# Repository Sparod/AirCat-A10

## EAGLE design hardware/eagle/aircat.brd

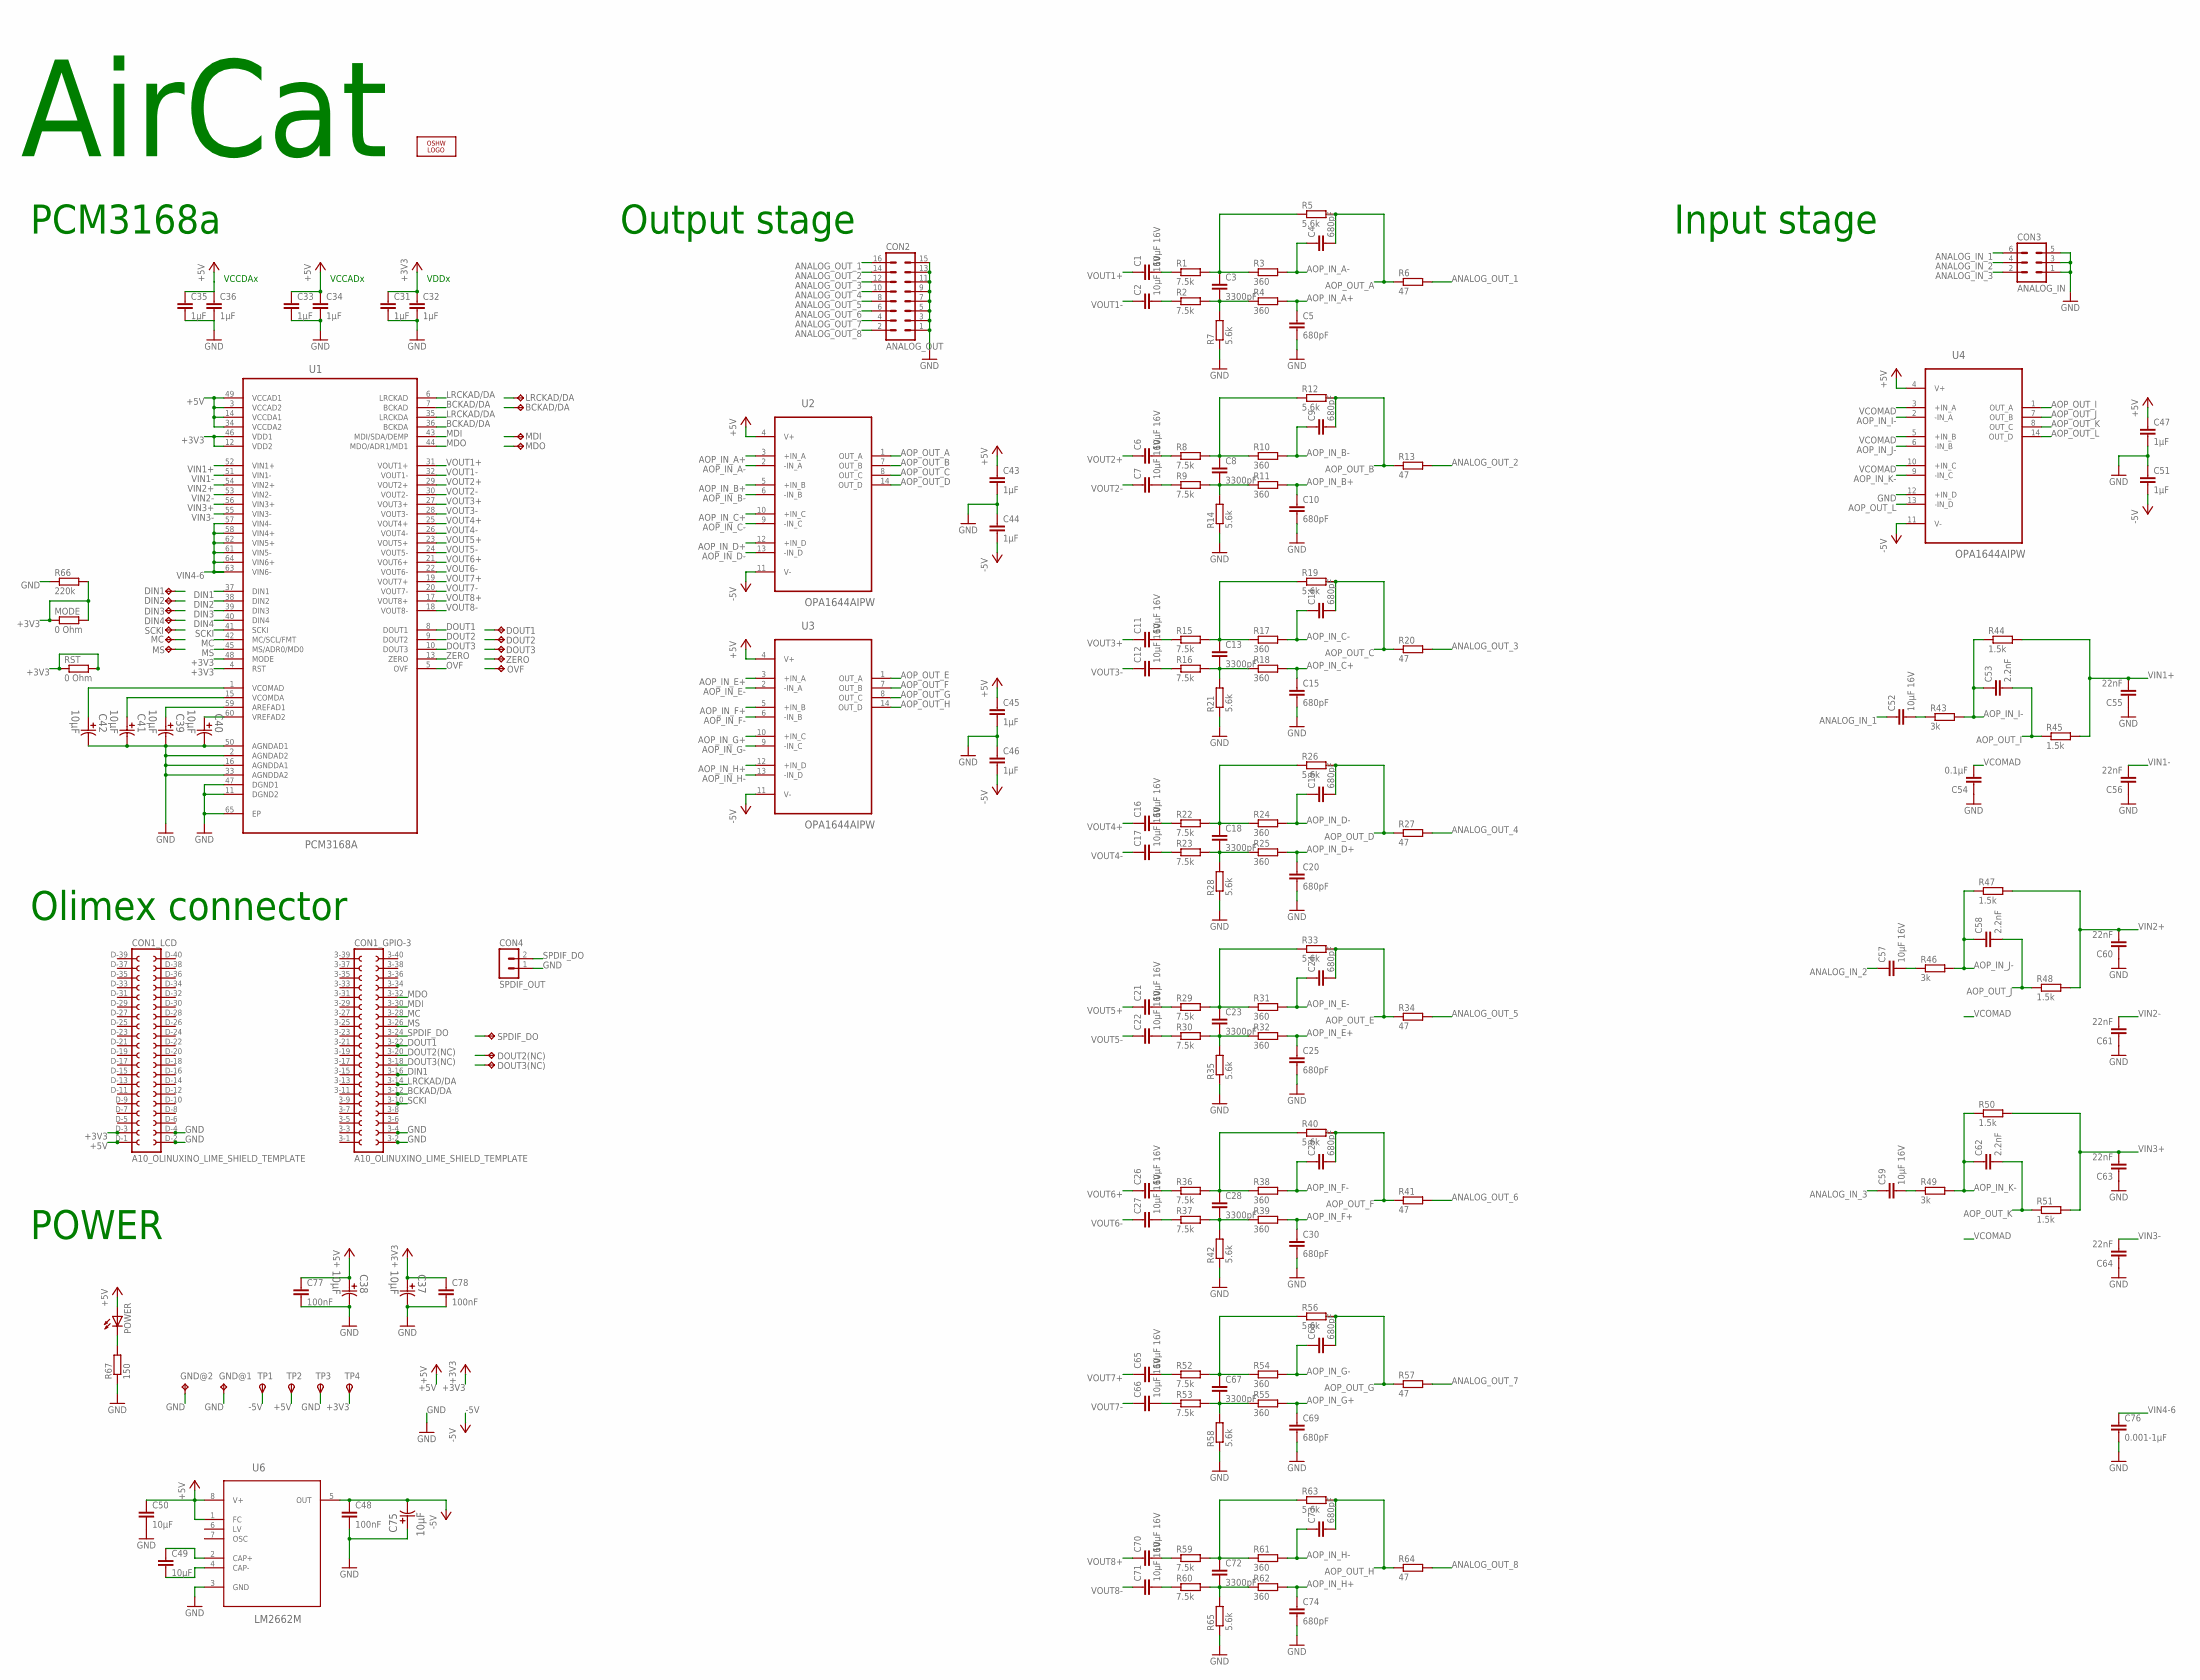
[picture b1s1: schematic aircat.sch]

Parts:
BCKAD/DA: TPTP10SQ; TP10SQ
C1, C2, C6, C7, C11, C12, C16, C17, C21, C22, C26, C27, C52, C57, C59, C65, C66, C70, C71: 10µF 16V; C0805; MPN 1206YD106KAT2A
C3, C8, C13, C18, C23, C28, C67, C72: 3300pF; C0603; MPN 06035C332KAT2A
C4, C5, C9, C10, C14, C15, C19, C20, C24, C25, C29, C30, C68, C69, C73, C74: 680pF; C0603; MPN C0603C681J5GACTU
C31, C32, C33, C34, C35, C36, C43, C44, C45, C46, C47, C51: 1µF; C0603; MPN 0603ZD105KAT2A
C37: 10µF; CAPAE430X610N; MPN EEEFK1V100UR
C38, C39, C40, C41, C42, C75: 10µF; CAPAE430X610N; TOLERANCE ±20 %; VOLTAGERATING 35V; MPN EEEFK1V100UR
C48: 100nF; C0603; MPN 10SVP10M
C49, C50: 10µF; C0805; MPN 10SVP10M
C53, C58, C62: 2.2nF; C0603; MPN 06035C222KAT2A
C54: 0.1µF; C0603; MPN 0402YD104KAT2A
C55, C56, C60, C61, C63, C64: 22nF; C0603; MPN 06033C223KAT2A
C76: 0.001-1µF; C0603
C77, C78: 100nF; C0603; MPN 06033D104KAT2A
CON1: A10_OLINUXINO_LIME_SHIELD_TEMPLATE; A10_OLINUXINO_LIME_SHIELD
CON2: ANALOG_OUT; MA08-2
CON3: ANALOG_IN; MA03-2
CON4: SPDIF_OUT; MA02-1
DIN1, DIN2, DIN3, DIN4: TPTP10SQ; TP10SQ
DOUT1, DOUT2, DOUT2(NC), DOUT3, DOUT3(NC): TPTP10SQ; TP10SQ
GND@1, GND@2: TPTP10SQ; TP10SQ
LOGO1: OSHW_LOGO_FILLX0200-NT; OSHW_FILLX200_NOTEXT
LRCKAD/DA: TPTP10SQ; TP10SQ
MC: TPTP10SQ; TP10SQ
MDI: TPTP10SQ; TP10SQ
MDO: TPTP10SQ; TP10SQ
MODE: 0 Ohm; R0603
MS: TPTP10SQ; TP10SQ
OVF: TPTP10SQ; TP10SQ
POWER: LEDSML0603; SML0603
R1, R2, R8, R9, R15, R16, R22, R23, R29, R30, R36, R37, R52, R53, R59, R60: 7.5k; R0603; MPN MCRE000161
R3, R4, R10, R11, R17, R18, R24, R25, R31, R32, R38, R39, R54, R55, R61, R62: 360; R0603
R5, R7, R12, R14, R19, R21, R26, R28, R33, R35, R40, R42, R56, R58, R63, R65: 5.6k; R0603; MPN MCPWR05FTEW5601
R6, R13, R20, R27, R34, R41, R57, R64: 47; R0603
R43, R46, R49: 3k; R0603; MPN 167I 3K TX 9 X 80 MM
R44, R45, R47, R48, R50, R51: 1.5k; R0603
R66: 220k; R0603
R67: 150; R0603; MPN MCRE000161
RST: 0 Ohm; R0603
SCKI: TPTP10SQ; TP10SQ
SPDIF_DO: TPTP10SQ; TP10SQ
TP1: -5V; B1,27
TP2: +5V; B1,27
TP3: GND; B1,27
TP4: +3V3; B1,27
U1: PCM3168A; QFP50P1200X1200X120-65N; MPN PCM3168APAP
U2, U3, U4: OPA1644AIPW; SOP65P640X120-14N; MPN OPA1644AIPW
U6: LM2662M; SOIC127P620X175-8N; MPN LM2662M
ZERO: TPTP10SQ; TP10SQ

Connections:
+3V3: C31.1, C32.1, C37.1, C78.1, CON1.D-3 (3), MODE.1, MODE.2, R66.2, RST.1, RST.2, TP4.TP, U1.4 (RST), U1.12 (VDD2), U1.46 (VDD1), U1.48 (MODE)
+5V: C33.1, C34.1, C35.1, C36.1, C38.1, C43.1, C45.1, C47.1, C50.1, C77.1, CON1.D-1 (1), POWER.A, TP2.TP, U1.3 (VCCAD2), U1.14 (VCCDA1), U1.34 (VCCDA2), U1.49 (VCCAD1), U2.4 (V+), U3.4 (V+), U4.4 (V+), U6.1 (FC), U6.8 (V+)
-5V: C44.2, C46.2, C48.1, C51.2, C75.2, TP1.TP, U2.11 (V-), U3.11 (V-), U4.11 (V-), U6.5 (OUT)
ANALOG_IN_1: C52.1, CON3.6
ANALOG_IN_2: C57.1, CON3.4
ANALOG_IN_3: C59.1, CON3.2
ANALOG_OUT_1: CON2.16, R6.2
ANALOG_OUT_2: CON2.14, R13.2
ANALOG_OUT_3: CON2.12, R20.2
ANALOG_OUT_4: CON2.10, R27.2
ANALOG_OUT_5: CON2.8, R34.2
ANALOG_OUT_6: CON2.6, R41.2
ANALOG_OUT_7: CON2.4, R57.2
ANALOG_OUT_8: CON2.2, R64.2
AOP_IN_A+: C5.1, R4.2, U2.3 (+IN_A)
AOP_IN_A-: C4.1, R3.2, U2.2 (-IN_A)
AOP_IN_B+: C10.1, R11.2, U2.5 (+IN_B)
AOP_IN_B-: C9.1, R10.2, U2.6 (-IN_B)
AOP_IN_C+: C15.1, R18.2, U2.10 (+IN_C)
AOP_IN_C-: C14.1, R17.2, U2.9 (-IN_C)
AOP_IN_D+: C20.1, R25.2, U2.12 (+IN_D)
AOP_IN_D-: C19.1, R24.2, U2.13 (-IN_D)
AOP_IN_E+: C25.1, R32.2, U3.3 (+IN_A)
AOP_IN_E-: C24.1, R31.2, U3.2 (-IN_A)
AOP_IN_F+: C30.1, R39.2, U3.5 (+IN_B)
AOP_IN_F-: C29.1, R38.2, U3.6 (-IN_B)
AOP_IN_G+: C69.1, R55.2, U3.10 (+IN_C)
AOP_IN_G-: C68.1, R54.2, U3.9 (-IN_C)
AOP_IN_H+: C74.1, R62.2, U3.12 (+IN_D)
AOP_IN_H-: C73.1, R61.2, U3.13 (-IN_D)
AOP_IN_I-: C53.1, R43.2, R44.1, U4.2 (-IN_A)
AOP_IN_J-: C58.1, R46.2, R47.1, U4.6 (-IN_B)
AOP_IN_K-: C62.1, R49.2, R50.1, U4.9 (-IN_C)
AOP_OUT_A: C4.2, R5.2, R6.1, U2.1 (OUT_A)
AOP_OUT_B: C9.2, R12.2, R13.1, U2.7 (OUT_B)
AOP_OUT_C: C14.2, R19.2, R20.1, U2.8 (OUT_C)
AOP_OUT_D: C19.2, R26.2, R27.1, U2.14 (OUT_D)
AOP_OUT_E: C24.2, R33.2, R34.1, U3.1 (OUT_A)
AOP_OUT_F: C29.2, R40.2, R41.1, U3.7 (OUT_B)
AOP_OUT_G: C68.2, R56.2, R57.1, U3.8 (OUT_C)
AOP_OUT_H: C73.2, R63.2, R64.1, U3.14 (OUT_D)
AOP_OUT_I: C53.2, R45.1, U4.1 (OUT_A)
AOP_OUT_J: C58.2, R48.1, U4.7 (OUT_B)
AOP_OUT_K: C62.2, R51.1, U4.8 (OUT_C)
AOP_OUT_L: U4.13 (-IN_D), U4.14 (OUT_D)
AREFAD1: C39.1, U1.59 (AREFAD1)
BCKAD/DA: BCKAD/DA.TP, CON1.3-12 (12), U1.7 (BCKAD), U1.36 (BCKDA)
DIN1: CON1.3-16 (16), DIN1.TP, U1.37 (DIN1)
DIN2: DIN2.TP, U1.38 (DIN2)
DIN3: DIN3.TP, U1.39 (DIN3)
DIN4: DIN4.TP, U1.40 (DIN4)
DOUT1: CON1.3-22 (22), DOUT1.TP, U1.8 (DOUT1)
DOUT2: DOUT2.TP, U1.9 (DOUT2)
DOUT2(NC): CON1.3-20 (20), DOUT2(NC).TP
DOUT3: DOUT3.TP, U1.10 (DOUT3)
DOUT3(NC): CON1.3-18 (18), DOUT3(NC).TP
GND: C5.2, C10.2, C15.2, C20.2, C25.2, C30.2, C31.2, C32.2, C33.2, C34.2, C35.2, C36.2, C37.2, C38.2, C39.2, C40.2, C41.2, C42.2, C43.2, C44.1, C45.2, C46.1, C47.2, C48.2, C50.2, C51.1, C54.1, C55.1, C56.1, C60.1, C61.1, C63.1, C64.1, C69.2, C74.2, C75.1, C76.2, C77.2, C78.2, CON1.3-2 (2), CON1.3-4 (4), CON1.D-2 (2), CON1.D-4 (4), CON2.1, CON2.3, CON2.5, CON2.7, CON2.9, CON2.11, CON2.13, CON2.15, CON3.1, CON3.3, CON3.5, CON4.1, GND@1.TP, GND@2.TP, R7.1, R14.1, R21.1, R28.1, R35.1, R42.1, R58.1, R65.1, R66.1, R67.1, TP3.TP, U1.2 (AGNDAD2), U1.11 (DGND2), U1.16 (AGNDDA1), U1.33 (AGNDDA2), U1.47 (DGND1), U1.50 (AGNDAD1), U1.65 (EP), U4.12 (+IN_D), U6.3 (GND)
LRCKAD/DA: CON1.3-14 (14), LRCKAD/DA.TP, U1.6 (LRCKAD), U1.35 (LRCKDA)
MC: CON1.3-28 (28), MC.TP, U1.42 (MC/SCL/FMT)
MDI: CON1.3-30 (30), MDI.TP, U1.43 (MDI/SDA/DEMP)
MDO: CON1.3-32 (32), MDO.TP, U1.44 (MDO/ADR1/MD1)
MS: CON1.3-26 (26), MS.TP, U1.45 (MS/ADR0/MD0)
unnamed: C2.2, R2.1
unnamed: C1.2, R1.1
unnamed: C3.1, R1.2, R3.1, R5.1
unnamed: C3.2, R2.2, R4.1, R7.2
unnamed: C7.2, R9.1
unnamed: C6.2, R8.1
unnamed: C8.1, R8.2, R10.1, R12.1
unnamed: C8.2, R9.2, R11.1, R14.2
unnamed: C12.2, R16.1
unnamed: C11.2, R15.1
unnamed: C13.1, R15.2, R17.1, R19.1
unnamed: C13.2, R16.2, R18.1, R21.2
unnamed: C17.2, R23.1
unnamed: C16.2, R22.1
unnamed: C18.1, R22.2, R24.1, R26.1
unnamed: C18.2, R23.2, R25.1, R28.2
unnamed: C22.2, R30.1
unnamed: C21.2, R29.1
unnamed: C23.1, R29.2, R31.1, R33.1
unnamed: C23.2, R30.2, R32.1, R35.2
unnamed: C27.2, R37.1
unnamed: C26.2, R36.1
unnamed: C28.1, R36.2, R38.1, R40.1
unnamed: C28.2, R37.2, R39.1, R42.2
unnamed: C52.2, R43.1
unnamed: C57.2, R46.1
unnamed: C59.2, R49.1
unnamed: C66.2, R53.1
unnamed: C65.2, R52.1
unnamed: C67.1, R52.2, R54.1, R56.1
unnamed: C67.2, R53.2, R55.1, R58.2
unnamed: C71.2, R60.1
unnamed: C70.2, R59.1
unnamed: C49.1, U6.2 (CAP+)
unnamed: C49.2, U6.4 (CAP-)
unnamed: C72.1, R59.2, R61.1, R63.1
unnamed: C72.2, R60.2, R62.1, R65.2
unnamed: POWER.C, R67.2
OVF: OVF.TP, U1.5 (OVF)
SCKI: CON1.3-10 (10), SCKI.TP, U1.41 (SCKI)
SPDIF_DO: CON1.3-24 (24), CON4.2, SPDIF_DO.TP
VCOMAD: C42.1, C54.2, U1.1 (VCOMAD), U4.3 (+IN_A), U4.5 (+IN_B), U4.10 (+IN_C)
VCOMDA: C41.1, U1.15 (VCOMDA)
VIN1+: C55.2, R44.2, R45.2, U1.52 (VIN1+)
VIN1-: C56.2, U1.51 (VIN1-)
VIN2+: C60.2, R47.2, R48.2, U1.54 (VIN2+)
VIN2-: C61.2, U1.53 (VIN2-)
VIN3+: C63.2, R50.2, R51.2, U1.56 (VIN3+)
VIN3-: C64.2, U1.55 (VIN3-)
VIN4-6: C76.1, U1.57 (VIN4-), U1.58 (VIN4+), U1.61 (VIN5-), U1.62 (VIN5+), U1.63 (VIN6-), U1.64 (VIN6+)
VOUT1+: C1.1, U1.31 (VOUT1+)
VOUT1-: C2.1, U1.32 (VOUT1-)
VOUT2+: C6.1, U1.29 (VOUT2+)
VOUT2-: C7.1, U1.30 (VOUT2-)
VOUT3+: C11.1, U1.27 (VOUT3+)
VOUT3-: C12.1, U1.28 (VOUT3-)
VOUT4+: C16.1, U1.25 (VOUT4+)
VOUT4-: C17.1, U1.26 (VOUT4-)
VOUT5+: C21.1, U1.23 (VOUT5+)
VOUT5-: C22.1, U1.24 (VOUT5-)
VOUT6+: C26.1, U1.21 (VOUT6+)
VOUT6-: C27.1, U1.22 (VOUT6-)
VOUT7+: C65.1, U1.19 (VOUT7+)
VOUT7-: C66.1, U1.20 (VOUT7-)
VOUT8+: C70.1, U1.17 (VOUT8+)
VOUT8-: C71.1, U1.18 (VOUT8-)
VREFAD2: C40.1, U1.60 (VREFAD2)
ZERO: U1.13 (ZERO), ZERO.TP

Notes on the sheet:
VCCDAx
VCCADx
VDDx
POWER
Olimex connector
PCM3168a
Output stage
Input stage
AirCat

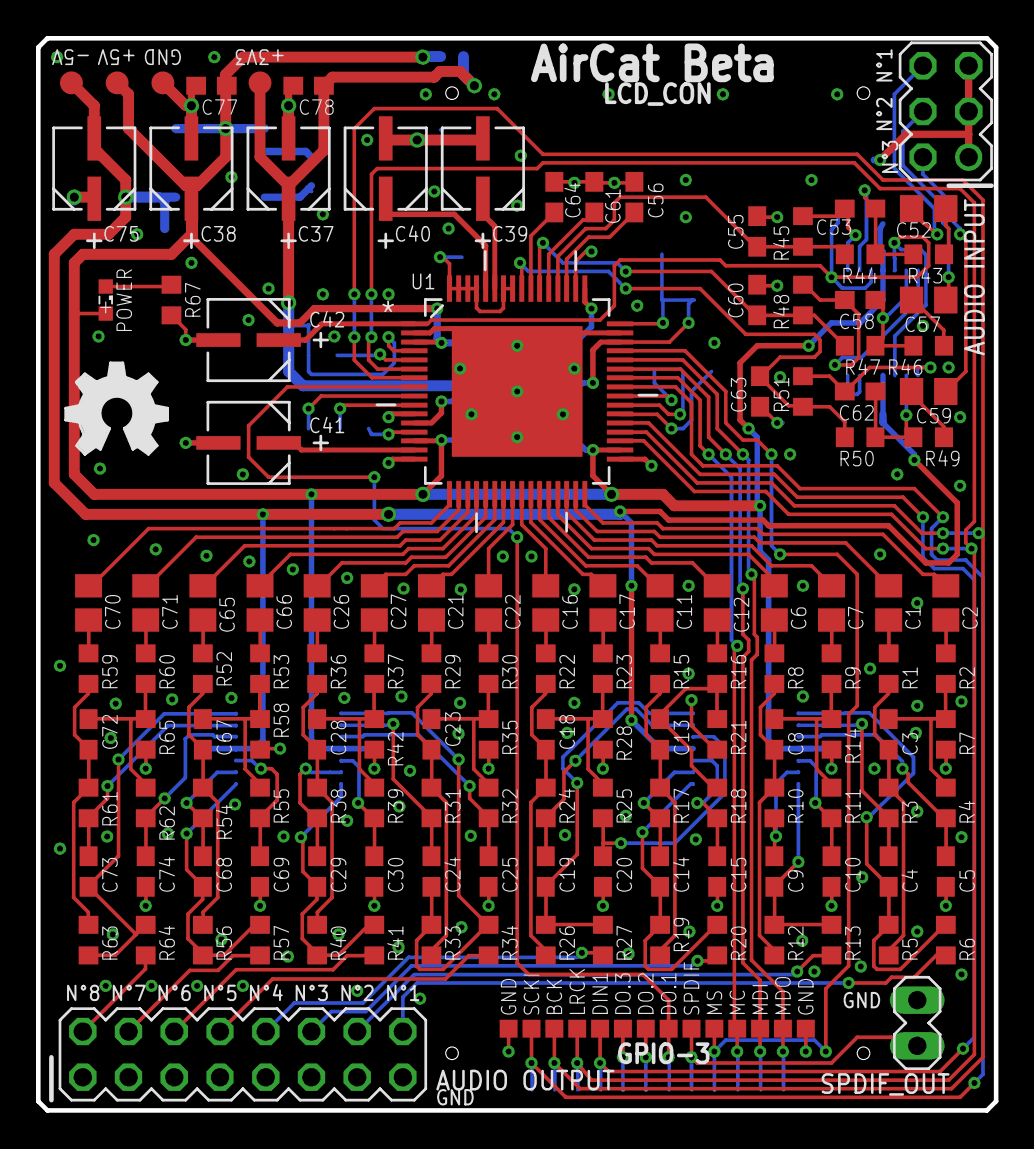
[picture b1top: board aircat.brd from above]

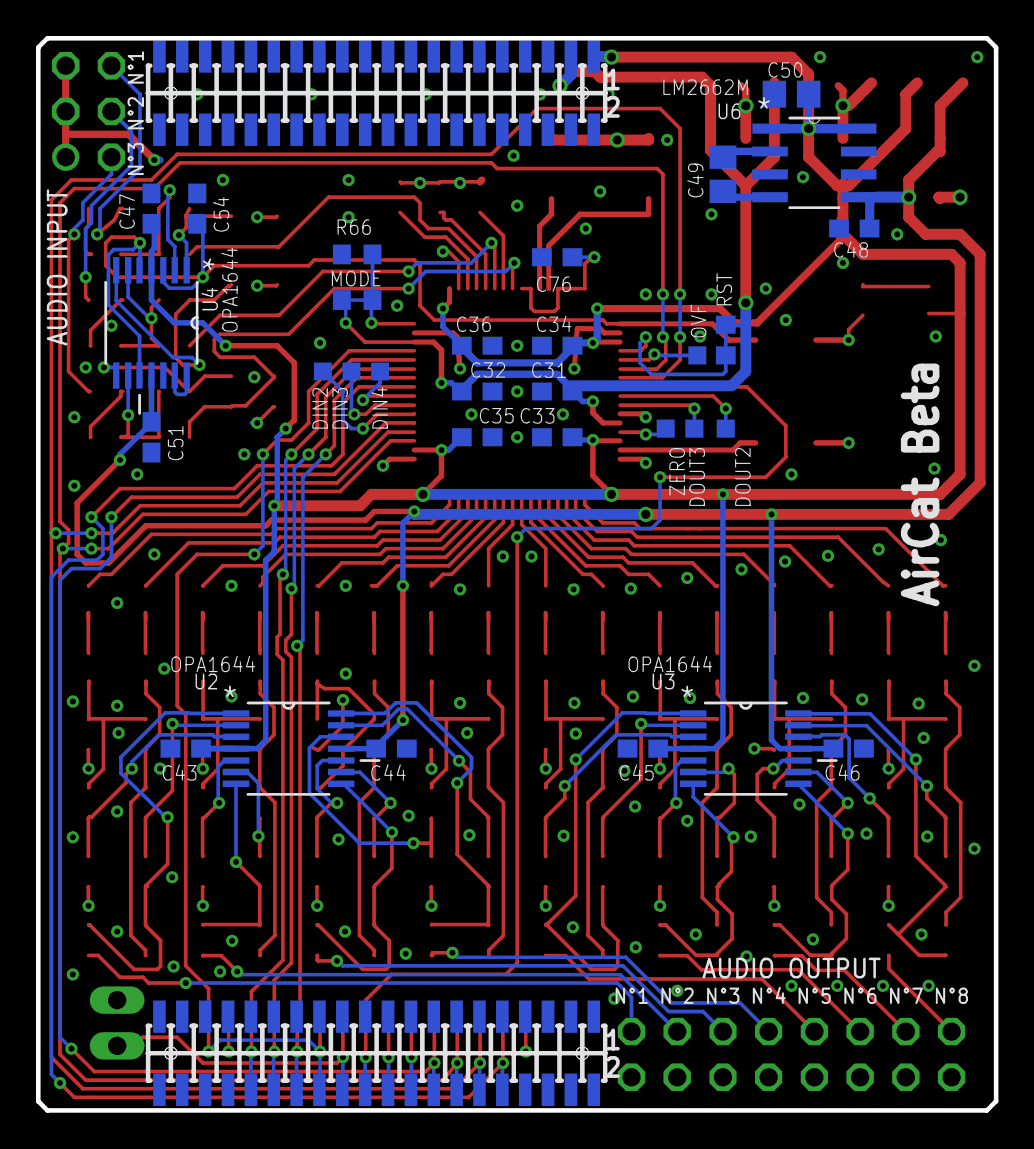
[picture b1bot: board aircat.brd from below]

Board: 2 copper layers, 53.2 x 59.6 mm, 183 parts (31 on the bottom side), 130 nets.

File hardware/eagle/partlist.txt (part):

Partlist

Exported from aircat.brd at 09/05/2014 18:37:59

EAGLE Version 6.1.0 Copyright (c) 1988-2012 CadSoft

Assembly variant: 

Part      Value                              Package                   Library                        Position (inch)       Orientation

BCKAD/DA                                     TP10SQ                    testpad                        (0.08125 -0.99375)    R0
C1        10µF 16V                           C0805                     rcl                            (0.8125 -0.0625)      R270
C2        10µF 16V                           C0805                     rcl                            (0.9375 -0.0625)      R270
C3        3300pF                             C0603                     rcl                            (0.8125 -0.35)        R90
C4        680pF                              C0603                     rcl                            (0.8125 -0.65)        R270
C5        680pF                              C0603                     rcl                            (0.9375 -0.65)        R270
C6        10µF 16V                           C0805                     rcl                            (0.5625 -0.0625)      R270
C7        10µF 16V                           C0805                     rcl                            (0.6875 -0.0625)      R270
C8        3300pF                             C0603                     rcl                            (0.5625 -0.35)        R90
C9        680pF                              C0603                     rcl                            (0.5625 -0.65)        R270
C10       680pF                              C0603                     rcl                            (0.6875 -0.65)        R270
C11       10µF 16V                           C0805                     rcl                            (0.3125 -0.0625)      R270
C12       10µF 16V                           C0805                     rcl                            (0.4375 -0.0625)      R270
C13       3300pF                             C0603                     rcl                            (0.3125 -0.35)        R90
C14       680pF                              C0603                     rcl                            (0.3125 -0.65)        R270
C15       680pF                              C0603                     rcl                            (0.4375 -0.65)        R270
C16       10µF 16V                           C0805                     rcl                            (0.0625 -0.0625)      R270
C17       10µF 16V                           C0805                     rcl                            (0.1875 -0.0625)      R270
C18       3300pF                             C0603                     rcl                            (0.0625 -0.35)        R90
C19       680pF                              C0603                     rcl                            (0.0625 -0.65)        R270
C20       680pF                              C0603                     rcl                            (0.1875 -0.65)        R270
C21       10µF 16V                           C0805                     rcl                            (-0.1875 -0.0625)     R270
C22       10µF 16V                           C0805                     rcl                            (-0.0625 -0.0625)     R270
C23       3300pF                             C0603                     rcl                            (-0.1875 -0.35)       R90
C24       680pF                              C0603                     rcl                            (-0.1875 -0.65)       R270
C25       680pF                              C0603                     rcl                            (-0.0625 -0.65)       R270
C26       10µF 16V                           C0805                     rcl                            (-0.4375 -0.0625)     R270
C27       10µF 16V                           C0805                     rcl                            (-0.3125 -0.0625)     R270
C28       3300pF                             C0603                     rcl                            (-0.4375 -0.35)       R90
C29       680pF                              C0603                     rcl                            (-0.4375 -0.65)       R270
C30       680pF                              C0603                     rcl                            (-0.3125 -0.65)       R270
C31       1µF                                C0603                     rcl                            (-0.0875 0.4)         MR180
C32       1µF                                C0603                     rcl                            (0.0875 0.4)          MR0
C33       1µF                                C0603                     rcl                            (-0.0875 0.3)         MR180
C34       1µF                                C0603                     rcl                            (-0.0875 0.5)         MR180
C35       1µF                                C0603                     rcl                            (0.0875 0.3)          MR0
C36       1µF                                C0603                     rcl                            (0.0875 0.5)          MR0
C37       10µF                               CAPAE430X610N             Panasonic-EEEFK_EEEFP          (-0.5 0.8875)         R90
C38       10µF                               CAPAE430X610N             Panasonic-EEEFK_EEEFP          (-0.7125 0.8875)      R90
C39       10µF                               CAPAE430X610N             Panasonic-EEEFK_EEEFP          (-0.075 0.8875)       R90
C40       10µF                               CAPAE430X610N             Panasonic-EEEFK_EEEFP          (-0.2875 0.8875)      R90
C41       10µF                               CAPAE430X610N             Panasonic-EEEFK_EEEFP          (-0.5875 0.2875)      R180
C42       10µF                               CAPAE430X610N             Panasonic-EEEFK_EEEFP          (-0.5875 0.5125)      R180
C43       1µF                                C0603                     rcl                            (0.725 -0.38125)      MR180
C44       1µF                                C0603                     rcl                            (0.275 -0.38125)      MR180
C45       1µF                                C0603                     rcl                            (-0.275 -0.38125)     MR180
C46       1µF                                C0603                     rcl                            (-0.725 -0.38125)     MR180
C47       1µF                                C0603                     rcl                            (0.8 0.8)             MR90
C48       100nF                              C0603                     rcl                            (-0.9 0.75)           MR180
C49       10µF                               C0805                     rcl                            (-0.65 0.875)         MR270
C50       10µF                               C0805                     rcl                            (-0.9 1.05)           MR180
C51       1µF                                C0603                     rcl                            (0.8 0.3)             MR90
C52       10µF 16V                           C0805                     rcl                            (0.9 0.8)             R0
C53       2.2nF                              C0603                     rcl                            (0.75 0.8)            R180
C54       0.1µF                              C0603                     rcl                            (0.7 0.8)             MR270
C55       22nF                               C0603                     rcl                            (0.525 0.75)          R270
C56       22nF                               C0603                     rcl                            (0.25625 0.825)       R270
C57       10µF 16V                           C0805                     rcl                            (0.9 0.6)             R180
C58       2.2nF                              C0603                     rcl                            (0.75 0.6)            R180
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
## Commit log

2014-04-27 Added initial .gitignore
2014-04-27 datasheets added
2014-04-27 commit initial. Eagle schematics and boards.
2014-04-27 pads added for unused pins
2014-04-27 Added A10 complete datasheet
2014-04-27 blacklisted eagle backup files
2014-04-27 Mode pin connection ok (VDD+pulldown)
2014-04-27 all data lines connected
2014-04-27 componant labels better placed
2014-04-27 export files updated
2014-04-27 airwire removed
2014-04-30 added IC's part name labels
2014-04-30 little data track path improvment
2014-04-30 change C48 capacitor
    switch from C0805 to C0603 form factor and from 10µF to 100nF value.
2014-05-01 changed 10µF capa form factor
    Changed 10µF 0603" package to 0805" because it's cheaper.
    Minor other optimizations were made too.
2014-05-01 added BOM - Bill of Material
2014-05-01 BOM corrected
    PCB was was wrong.
    File was corrupted.
2014-05-01 added excel backup file to blacklist
2014-05-01 updated OSHpark PCB price for volume production
    PCB price is 5x lower if order is > 150 square inches
2014-05-01 minor ground plane optimization
2014-05-08 added power indicating led
    fix #1
    added green led to indicate power on the 5V rail.
2014-05-08 added SPDIF OUT connector
    fix #4
2014-05-09 improved the component value labels
2014-05-09 fix olimex header genre to female
    The two Olimex 2x20 pins 1.27" pitch has been changed from male to
    female.
2014-05-09 fixed BOM capacitor reference
    removed the Tape & Reel service, which has a 100+ minimun order number.
2014-05-09 added test points for data lines
    fix #7
2014-05-09 fixed text alignment issue
    fix #8
    workaround: as no real solution was found, componant name labels were
    all sat to 'bottom-left' alignment and re-positioned by hand.
2014-05-09 added test points for unused data lines
    fix #7
2014-05-09 minor electrical line path optimizations
2014-05-09 relocated componant laying around GPIO-4
    fix #9
    LM2662 and its capacitors having relocated in order not to enter in
    contact with the GPIO-4 connector.
2014-05-09 added Eagle library files
2014-05-09 fixed BOM taxes issues
    fix #5
    Order in US Dollars are converted in Euros.
    French Taxes (VAT) is added in grand total.
2014-05-09 fixed incorrect capacitor reference in BOM
2014-05-09 added
    componant command basket export from fr.farnell.com
2014-05-09 added licence logo
    fix #6
2014-05-09 updated pcb images
2014-05-09 updated OSHpark pcb image
2014-05-09 updated order information
2014-05-09 corrected BOM pcb price
2014-05-09 Updated BOM and Farnell basket
2014-05-10 fixed minor unrouted line and typo
2014-05-10 changed Alpha to Beta title
2014-05-19 added ground plane on the top layer
    added ground plane on the top layer, for better imunization to EMI.
